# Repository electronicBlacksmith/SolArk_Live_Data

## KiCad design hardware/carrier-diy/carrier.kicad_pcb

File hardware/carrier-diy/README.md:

# SolArk XIAO tap carrier, Rev B-diy (2026-10-13)

This is a small 4-layer carrier PCB. It replaces the hand-wired protoboard in
[`../../docs/hardware/README.md`](../../docs/hardware/README.md) and holds:
- a XIAO ESP32S3 Plus, soldered on header pins;
- a 12 V to 5 V buck regulator with input protection;
- a receive-only Schmitt buffer for the two passive Modbus taps.

The harness is soldered straight to six wire pads (J1). Its in-line plug lives on the harness.

This is the **hand-soldered, lowest-cash variant**. Every fitted part is 0603 or larger, with leaded or visible terminations.
- Recommended build: OSH Park 4-layer bare boards, with every part hand-soldered from Digi-Key. Costs are in `PRICING.md`.
- Changes from Rev A: `CHANGES-revB.md`.
- Unresolved items: `OPEN-ITEMS.md`.

Status: **design complete, not ordered.**
- `sh scripts/build.sh` exits 0.
- ERC reports 0 violations; DRC reports 0 violations, 0 unconnected items and 0 schematic parity issues. Both run at all severities, so warnings count. The reports are `fab/erc.rpt` and `fab/drc.rpt`.

| | |
|---|---|
| Board | **29.0 x 30.0 mm** (x along the J1 edge, y along the USB-C edge), 4 layers, 1.6 mm FR-4 |
| Assembly | Everything hand-soldered. All fitted SMD parts are on the top. The bottom holds only the DNP proxy pads and the header/wire-pad joints. |
| Height | About 7.8 mm (1.0 mm tail + 1.6 mm board + 0.3 mm + 4.9 mm XIAO) against a 9.0 mm limit [I]. Measure before ordering: `OPEN-ITEMS.md` O1. |

Other renders: `fab/render_bottom.png`, `fab/render_side_front.png`, `fab/render_side_right.png` and `fab/render_iso.png`.

## !! J1 OFF FOR USB !!

**Unsolder or unplug the harness (J1) before connecting USB-C to the XIAO.** This rule is also on the bottom silk.
- D2 blocks the XIAO's USB 5 V from reaching the buck.
- USB still ties the laptop's ground to the inverter ground through J1.
- Flash and debug the XIAO on the bench, with the harness unplugged at its in-line connector.

## Files

| Path | What |
|---|---|
| `carrier.kicad_pro` / `.kicad_sch` / `.kicad_pcb` | KiCad 10 project. Every DRC minimum (ring, clearance, track, hole, hole to hole, edge) is the stricter of the JLCPCB 4-layer and OSH Park 4-layer published values, so a clean DRC holds for either fab. |
| `scripts/design.py` | **Single source of truth**: parts, values, sources (Digi-Key/LCSC), the hand kit, DNP flags, nets and the VBUS tolerance inputs |
| `scripts/gen_lib.py` | Project symbols and footprints: XIAO header footprint, J1 wire pads, TI DBV0006A, Bourns SRP4020TA and MF-MSMF lands, box 3D models |
| `scripts/gen_sch.py`, `gen_pcb.py`, `routes.py` | Schematic; placement, routing, pours, silk and stackup |
| `scripts/build.sh` | Full regeneration, ERC, DRC (fails on any violation) and all fab exports |
| `tests/` | Design and board invariants (run `../../tools/.venv/bin/pytest -q tests`) |
| `fab/carrier_gerbers.zip` | Gerbers, drill file and job file. This is the file you upload to OSH Park or JLC. |
| `fab/carrier_bom_digikey.csv` | Digi-Key order for every fitted part, plus the header pins, the harness plug and the 2 harness 10 k resistors (rows marked `kit`) |
| `fab/carrier_bom_jlc.csv`, `fab/carrier_cpl_jlc.csv` | Only for route (a), JLC Economic placing the Basic parts. See `PRICING.md`. |
| `fab/carrier_schematic.pdf` | Schematic |

The generator overwrites the KiCad files. To change the design, edit `scripts/design.py` (and `routes.py` for copper), never the KiCad files.

## Circuit

```
J1.1 +12V -> F1 PPTC 0.5A/60V (1812) -> D1 B5819W -> +12V_P [TVS1 SMF18A, C1 10uF/50V, C2 100nF]
  -> U2 LMR51610 (EN = VIN, 1.1 MHz) -> L1 SRP4020TA 10uH -> +5V_BUCK [C7 22uF/25V, R13 20.5k / R14 3.83k 0.1 %]
  -> D2 PMEG4030ER (backfeed block) -> +5V_X [C3 100uF, C4 100nF] -> XIAO 5V (pin 14)

J1.5 TAP pad 9  (inverter replies) -> R3 1k -> U3 1A [R5 100k to 3V3] -> U3 1Y -> R7 1k -> XIAO D0/GPIO1 (pin 1)
J1.6 TAP pad 10 (dongle requests)  -> R4 1k -> U3 2A [R6 100k to 3V3] -> U3 2Y -> R8 1k -> XIAO D1/GPIO2 (pin 2)
U3 SN74LVC2G17 on XIAO 3V3 [C9 100nF]
XIAO D9/GPIO8 (pin 10) -> R12 1k DNP -> JP1 open jumper -> TP1 pad   (bottom, "DNP: proxy only")
```

**Receive only.**
- The XIAO GPIOs see only U3's outputs. The taps see only U3's inputs and the series resistors.
- No path through fitted parts lets the board drive the tapped lines.
- U3 has Ioff, so a powered-down board does not load the link.
- The off-board 10 k resistors in the harness are **required** (kit item CF18JT10K0). Board B has no ESD diodes; that is acceptable only with these 10 k in series at the dongle end of each tap wire.
- `tests/test_design.py` enforces all of this.

**Bias.**
- R5/R6 hold the buffer inputs high when the harness is unplugged.
- A tap low gives 0.33 V at the U3 input, below VT− min of 0.8 V. A tap high gives about 3.3 V, above VT+ max of 2.0 V.

**Vout.** 0.8 x (1 + 20.5/3.83) = 5.08 V nominal, 4.985-5.180 V worst case. The XIAO pin sees 4.485-5.180 V after D2 (arithmetic in `CHANGES-revB.md`).

**J1 wire pads**: 6 plated holes, 1.0 mm drill and 1.8 mm pads, on 2.54 mm pitch along the bottom edge. Pin 1 has the square pad.

| Pin | Signal |
|---|---|
| 1 | +12 V |
| 2 | GND (power) |
| 3 | spare, NC |
| 4 | GND (signal) |
| 5 | TAP pad 9 (inverter replies) |
| 6 | TAP pad 10 (dongle requests) |

The harness:
- **Required: one 10 k series resistor in each tap wire** (Stackpole CF18JT10K0, 1/8 W axial, Digi-Key CF18JT10K0CT-ND, in the kit). Solder it at the **dongle-pad end**: one at dongle pad 9 (J1.5 wire) and one at dongle pad 10 (J1.6 wire), heat-shrunk. They are not optional: they are the ESD and fault limit on the tap lines, since Board B has no D3/D4 diodes. Without them, do not connect the harness.
- Solder 6 short wires (26-24 AWG) into J1.
- Break a **6-pin section off a PRPC040 strip, keeping its plastic**, and solder the free ends of the 6 J1 wires to its short tails. Heat-shrink each joint. This half stays with the carrier.
- It mates with the Sullins PPTC061LFBN-RC 6-way female housing. Solder the dongle-side wires to the housing's tails.
- Keep the inline fuse at the DB9 end, because F1 does not protect the harness itself.

The wire bend leaves the J1 edge, past the board outline (O2).

## XIAO mount

The XIAO is soldered on **Sullins PRPC040SAAN-RC** 0.64 mm square header pins (break off 2 x 7).
- The carrier holes are drilled 1.10 mm, which is 1.02-1.23 mm finished at JLC's +0.13/−0.08 tolerance and tighter at OSH Park's.
- The worst-case pin diagonal is 0.933 mm.
- The castellation pads are gone. The 1.45 mm top ring clears the Plus's bottom pads 15-23 by 0.174 mm.
- **The XIAO is not removable.** Desoldering 14 pins is possible but rough on the board.

## Hand-assembly order

You need:
- a temperature-controlled iron with a fine conical tip and a 2-3 mm chisel tip;
- flux, 0.5 mm solder, tweezers and solder wick;
- a magnifier;
- optionally, hot air.

Work from the smallest, flattest parts to the tallest. Keep the hot-air nozzle away from finished 0603s.

1. **U3, U2 (SOT-23-6), iron, fine tip.** Tack one corner pin, check alignment and **pin 1** against the silk dot and the render, then solder the rest. Wick any bridges.
2. **0603 resistors and capacitors, iron, fine tip.**
   - The R3-R8 columns are on the left; R13/R14 and C8 sit by U2.
   - **R13 = 20.5k and R14 = 3.83k are the 0.1 % parts.** Do not swap them with the 1 % strip.
3. **Diodes, iron. Check the polarity band against the silk before soldering.**
   - D1 B5819W (SOD-123) and TVS1 SMF18A (SOD-123FL) sit in the left protection stack.
   - D2 PMEG4030ER (CFP3) sits next to the USB edge.
4. **1206 capacitors C1, C3, C7, iron, chisel tip.** These need more heat.
5. **F1 1812 PPTC, chisel tip.**
6. **L1 SRP4020TA.** Use the chisel tip with plenty of heat on each terminal, or hot air at about 350 °C. Its pads extend past the body, so an iron works.
7. **Clean the flux and inspect** under magnification.
8. **Power test, no XIAO.**
   - Feed 12 V into J1 pin 1 (+) and pin 2 (−) from a supply limited to **100 mA**.
   - Expect under about 10 mA idle.
   - Expect 4.99-5.18 V at C7 and 4.8-5.18 V at C3 (XIAO pin 14). With no load, D2 drops only about 0.1-0.2 V.
   - Swap the polarity: there should be no current, because D1 blocks it.
9. **Header pins and XIAO.**
   - Insert the 2 x 7 header strips into the XIAO and seat them on the carrier.
   - Solder the XIAO side first, then the carrier side from the bottom.
   - **Pull off the black plastic spacer** (it would add 2.5 mm). The XIAO should sit about 0.3 mm above the board.
   - Trim the tails to about 1.0 mm below the board.
   - USB-C goes at the edge marked "USB".
10. **Re-check 5 V at XIAO pin 14** with the XIAO running.
11. **Harness.** Solder the 6 wires into J1 per the pin table and fit the in-line plug. Fit the two **required** 10 k resistors at the dongle-pad ends of the J1.5 and J1.6 wires. Check continuity (dongle pad 9 to J1.5 and pad 10 to J1.6 read 10 k) and that there is no 12 V to tap short before connecting to the dongle.

## Verified vs inferred

**Verified** from primary sources or tool output on 2026-10-13, and for C3, the harness 10 k and the fab rules on 2026-10-14. URLs are in `CHANGES-revB.md`.
- ERC, DRC and parity are clean.
- Every fitted part:
  - is in stock at Digi-Key, with the part number and price;
  - has its land pattern matched to the manufacturer drawing and enforced by `test_land_patterns_match_the_datasheets` (the generic 0603/1206 passives use KiCad's IPC lands; C3's differs from TDK's recommendation);
  - is within its voltage and current ratings.
- LMR51610 pinout, VFB tolerance, current limit and FB divider range (TI).
- SN74LVC2G17 pinout, thresholds and Ioff (TI).
- Sullins PRPC040 pin size and insulator height.
- OSH Park and JLC 4-layer rules (every DRC minimum is the stricter of the two) and the OSH Park price; JLC Economic PCBA fees.
- C3 (TDK C3216X5R0J107M160AB) stock, rating and 5 V bias (about 28.7 µF). Its land is KiCad's 1206, which is not TDK's recommended land (see `CHANGES-revB.md`).
- XIAO pin positions, outline and Plus pad positions, from Seeed's KiCad files.

**Inferred**, still to verify (see `OPEN-ITEMS.md`):
- XIAO Plus total height (4.9 mm) and the stack numbers.
- The USB 4.40 V low-power minimum used for the VBUS floor.
- The PMEG4030ER forward voltage at 0.5 A when cold.
- PPTC hold current at 60 °C.
- The dongle's logic level (assumed 3.3 V; 5 V also works).

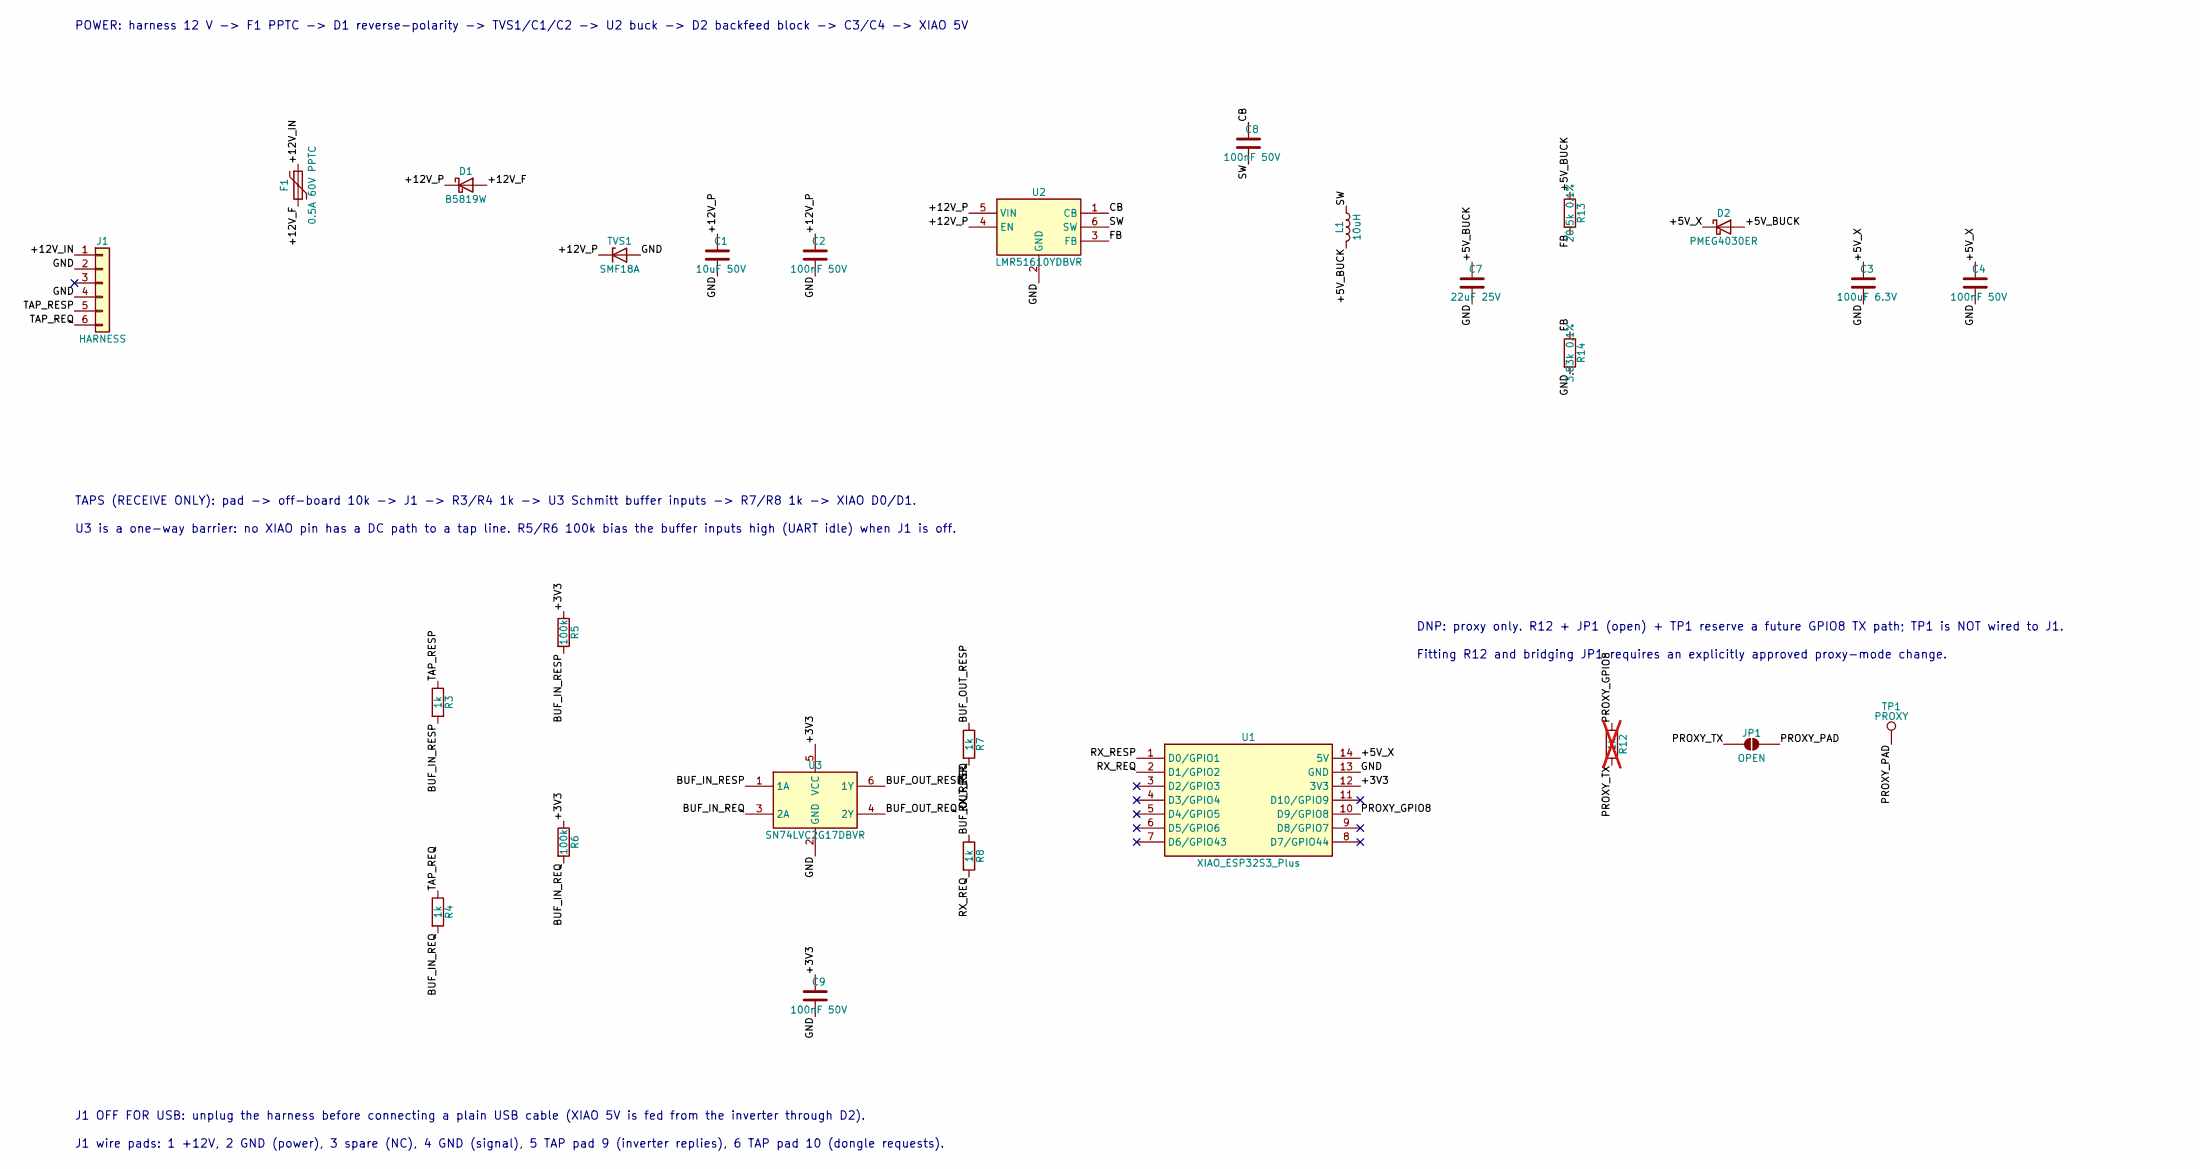
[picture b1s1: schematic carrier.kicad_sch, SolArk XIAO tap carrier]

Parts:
C1: 10uF 50V; C_1206_3216Metric; LCSC C13585
C2, C4, C8, C9: 100nF 50V; C_0603_1608Metric; LCSC C14663
C3: 100uF 6.3V; C_1206_3216Metric; LCSC C15008
C7: 22uF 25V; C_1206_3216Metric
D1: B5819W; D_SOD-123; LCSC C8598
D2: PMEG4030ER; Nexperia_CFP3_SOD-123W
F1: 0.5A 60V PPTC; Fuse_1812_Bourns_MF-MSMF
J1: HARNESS; WirePads_1x06_P2.54
JP1: OPEN; SolderJumper-2_P1.3mm_Open_RoundedPad1.0x1.5mm
L1: 10uH; L_Bourns_SRP4020TA
R3, R4, R7, R8: 1k; R_0603_1608Metric; LCSC C21190
R5, R6: 100k; R_0603_1608Metric; LCSC C25803
R12: 1k; R_0603_1608Metric; LCSC C21190; not fitted
R13: 20.5k 0.1%; R_0603_1608Metric
R14: 3.83k 0.1%; R_0603_1608Metric
TP1: PROXY; TestPoint_Pad_D1.0mm
TVS1: SMF18A; D_SOD-123FL_Littelfuse_SMF
U1: XIAO_ESP32S3_Plus; XIAO_ESP32S3_Header_THT
U2: LMR51610YDBVR; SOT-23-6_TI_DBV0006A
U3: SN74LVC2G17DBVR; SOT-23-6_TI_DBV0006A

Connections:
/+3V3: C9.1, R5.1, R6.1, U1.12 (3V3), U3.5 (VCC)
/+5V_BUCK: C7.1, D2.2 (A), L1.2, R13.1
/+5V_X: C3.1, C4.1, D2.1 (K), U1.14 (5V)
/+12V_F: D1.2 (A), F1.2
/+12V_IN: F1.1, J1.1
/+12V_P: C1.1, C2.1, D1.1 (K), TVS1.1 (K), U2.4 (EN), U2.5 (VIN)
/BUF_IN_REQ: R4.2, R6.2, U3.3 (2A)
/BUF_IN_RESP: R3.2, R5.2, U3.1 (1A)
/BUF_OUT_REQ: R8.1, U3.4 (2Y)
/BUF_OUT_RESP: R7.1, U3.6 (1Y)
/CB: C8.1, U2.1 (CB)
/FB: R13.2, R14.1, U2.3 (FB)
/GND: C1.2, C2.2, C3.2, C4.2, C7.2, C9.2, J1.2, J1.4, R14.2, TVS1.2 (A), U1.13 (GND), U2.2 (GND), U3.2 (GND)
/PROXY_GPIO8: R12.1, U1.10 (D9/GPIO8)
/PROXY_PAD: JP1.2 (B), TP1.1
/PROXY_TX: JP1.1 (A), R12.2
/RX_REQ: R8.2, U1.2 (D1/GPIO2)
/RX_RESP: R7.2, U1.1 (D0/GPIO1)
/SW: C8.2, L1.1, U2.6 (SW)
/TAP_REQ: J1.6, R4.1
/TAP_RESP: J1.5, R3.1

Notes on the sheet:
POWER: harness 12 V -> F1 PPTC -> D1 reverse-polarity -> TVS1/C1/C2 -> U2 buck -> D2 backfeed block -> C3/C4 -> XIAO 5V
TAPS (RECEIVE ONLY): pad -> off-board 10k -> J1 -> R3/R4 1k -> U3 Schmitt buffer inputs -> R7/R8 1k -> XIAO D0/D1.
U3 is a one-way barrier: no XIAO pin has a DC path to a tap line. R5/R6 100k bias the buffer inputs high (UART idle) when J1 is off.
DNP: proxy only. R12 + JP1 (open) + TP1 reserve a future GPIO8 TX path; TP1 is NOT wired to J1.
Fitting R12 and bridging JP1 requires an explicitly approved proxy-mode change.
J1 OFF FOR USB: unplug the harness before connecting a plain USB cable (XIAO 5V is fed from the inverter through D2).
J1 wire pads: 1 +12V, 2 GND (power), 3 spare (NC), 4 GND (signal), 5 TAP pad 9 (inverter replies), 6 TAP pad 10 (dongle requests).

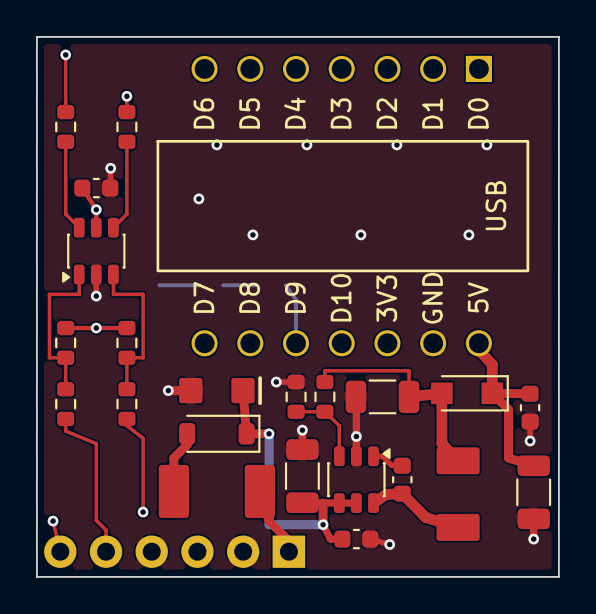
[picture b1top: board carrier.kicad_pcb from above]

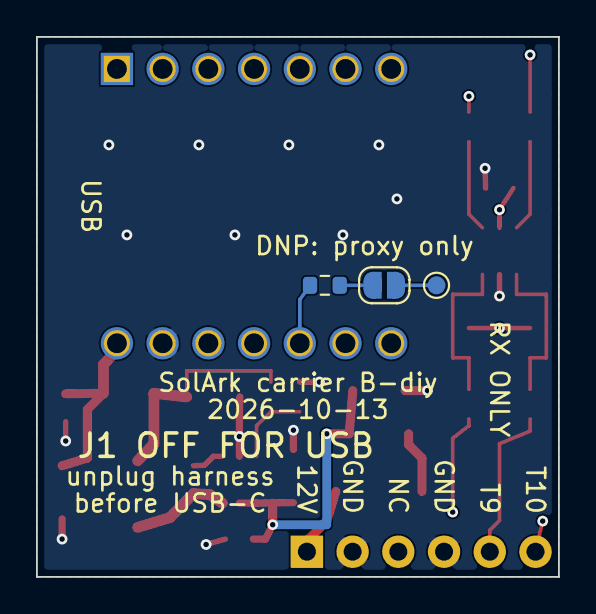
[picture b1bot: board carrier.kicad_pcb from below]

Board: 4 copper layers, 29.0 x 30.0 mm, 27 parts (3 on the bottom side), 21 nets.

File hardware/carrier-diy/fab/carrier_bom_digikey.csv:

"Digi-Key PN","MPN","Qty per board","Designators","Value","Footprint","Route (a) fit"
"118-MF-MSMF050/60X-2CT-ND","Bourns MF-MSMF050/60X-2","1","F1","0.5A 60V PPTC","Fuse_1812_Bourns_MF-MSMF","hand"
"B5819W-TPMSCT-ND","MCC B5819W-TP (JLC: CJ B5819W C8598)","1","D1","B5819W","D_SOD-123","jlc"
"F5820CT-ND","Littelfuse SMF18A","1","TVS1","SMF18A","D_SOD-123FL_Littelfuse_SMF","hand"
"13-CC1206KKX5R9BB106CT-ND","Yageo CC1206KKX5R9BB106 (JLC: Samsung CL31A106KBHNNNE)","1","C1","10uF 50V","C_1206_3216Metric","jlc"
"311-1344-1-ND","Yageo CC0603KRX7R9BB104","4","C2,C8,C4,C9","100nF 50V","C_0603_1608Metric","jlc"
"296-LMR51610YDBVRCT-ND","TI LMR51610YDBVR","1","U2","LMR51610YDBVR","SOT-23-6_TI_DBV0006A","hand"
"SRP4020TA-100MCT-ND","Bourns SRP4020TA-100M","1","L1","10uH","L_Bourns_SRP4020TA","hand"
"587-3246-1-ND","Taiyo Yuden TMK316BBJ226ML-T","1","C7","22uF 25V","C_1206_3216Metric","hand"
"P20.5KDBCT-ND","Panasonic ERA-3AEB2052V","1","R13","20.5k 0.1%","R_0603_1608Metric","hand"
"P3.83KDBCT-ND","Panasonic ERA-3AEB3831V","1","R14","3.83k 0.1%","R_0603_1608Metric","hand"
"1727-5313-1-ND","Nexperia PMEG4030ER,115","1","D2","PMEG4030ER","Nexperia_CFP3_SOD-123W","hand"
"445-6008-1-ND","TDK C3216X5R0J107M160AB (JLC: Samsung CL31A107MQHNNNE)","1","C3","100uF 6.3V","C_1206_3216Metric","jlc"
"311-1.00KHRCT-ND","Yageo RC0603FR-071KL (JLC: Uniroyal 0603WAF1001T5E)","4","R3,R4,R7,R8","1k","R_0603_1608Metric","jlc"
"311-100KHRCT-ND","Yageo RC0603FR-07100KL (JLC: Uniroyal 0603WAF1003T5E)","2","R5,R6","100k","R_0603_1608Metric","jlc"
"296-SN74LVC2G17DBVRCT-ND","TI SN74LVC2G17DBVR","1","U3","SN74LVC2G17DBVR","SOT-23-6_TI_DBV0006A","hand"
"S1011EC-40-ND","Sullins PRPC040SAAN-RC","2x7 pins","-","U1 mount: 0.64 mm square header pins, plastic removed after soldering","-","kit"
"S7004-ND","Sullins PPTC061LFBN-RC","1","-","Harness in-line plug (female); mates with a 6-pin PRPC040 section (plastic kept) on the J1 wires","-","kit"
"CF18JT10K0CT-ND","Stackpole CF18JT10K0","2","-","REQUIRED harness series 10 k, 1/8 W axial: one in each tap wire, at the dongle pad 9 and pad 10 ends","-","kit"

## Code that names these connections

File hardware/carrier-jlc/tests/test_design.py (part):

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    # Without the buffer, no tap reaches any XIAO GPIO.
    assert not (walk(TAPS, use_buffer=False) & gpio_nets())
    # With the buffer, both taps reach exactly their RX pins.
    assert walk({"TAP_RESP"}, use_buffer=True) & gpio_nets() == {"RX_RESP"}
    assert walk({"TAP_REQ"}, use_buffer=True) & gpio_nets() == {"RX_REQ"}


def test_no_gpio_can_reach_a_tap() -> None:
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

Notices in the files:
parts and their libraries:
XIAO ESP32S3 (Plus) edge pins on soldered 2.54 mm header pins (0.64 mm square): 1.1 mm PTH, small 1.45 mm top ring under the XIAO, 1.8 mm solder-side ring. Derived from Seeed XIAO-ESP32-S3-DIP (CC BY-SA 4.0).
